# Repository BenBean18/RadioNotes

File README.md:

# KQ4TVW's radio notes
This is an attempt to put much of the random radio knowledge I'm trying to collect in one place for future reference. Radio is really hard and there are so many different things to understand and keep track of, so I thought I'd create a journal thing. Not sure where this is going to go, but I'll probably update this README when I find out :)

## Topics
- [Signal processing](dsp/)
- [Antenna design](antenna/)
- [Amplifier design](amplifier/)
- [Filter design](filter/)
- [Practical usage/application (tools, resources, etc)](application/)

I'm sure I'll think of more things to add, this is a WIP.

## Useful general resources
- https://pysdr.org/index.html
- https://www.electronics-notes.com/articles/radio/rf-mixer/fet-rf-mixer.php
- https://hackaday.com/2020/07/17/modern-radio-receiver-architecture-from-regenerative-to-direct-conversion/
- https://people.physics.anu.edu.au/~dxt103/160m/class_E_amplifier_design.pdf SATURATION VOLTAGE IS ZERO FOR A FET 

## [Journal](journal/)

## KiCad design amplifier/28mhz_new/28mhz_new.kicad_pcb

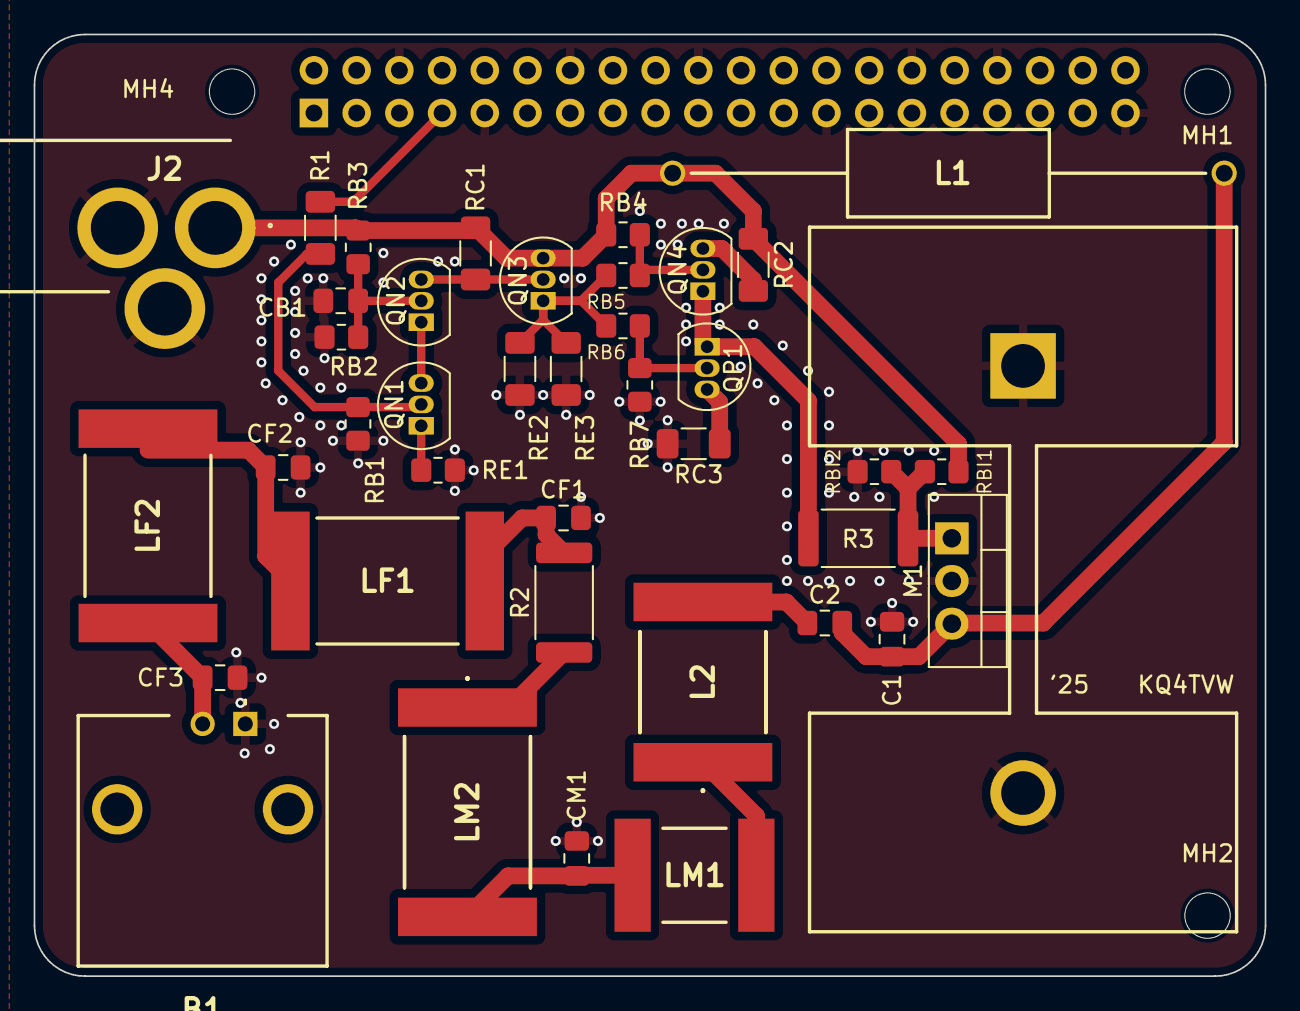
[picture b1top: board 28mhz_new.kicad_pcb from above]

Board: 2 copper layers, 73.2 x 56.0 mm, 44 parts (1 on the bottom side), 25 nets.

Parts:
B1: CONBNC002
C1: 220p; C_0805_2012Metric_Pad1.18x1.45mm_HandSolder
C2: 110p; C_0805_2012Metric_Pad1.18x1.45mm_HandSolder
CB1: 0.022µ; C_0805_2012Metric_Pad1.18x1.45mm_HandSolder
CF1, CF3: 120p; C_0805_2012Metric_Pad1.18x1.45mm_HandSolder
CF2: 220p; C_0805_2012Metric_Pad1.18x1.45mm_HandSolder
CM1: 220p; C_0805_2012Metric_Pad1.18x1.45mm_HandSolder
H1: 647-25ABPE; 64725ABPE
J1: GPIO; PinSocket_2x20_P2.54mm_Vertical
J2: 694106301002; 694106301002_1
L1: 10µ; INDAD3280W80L1200D520
L2: 330n; 2929SQ331GEC
LF1, LF2: 390n; 2929SQ391GEC
LM1: 180n; 2222SQ181JEC
LM2: 430n; 2929SQ431GEC
M1: RD16HHF1; TO-220-3_Vertical
MH1, MH2, MH4: MountingHole_2.7mm_M2.5
QN1, QN2, QN3, QN4: 2N3904; TO-92L_Inline
QP1: 2N3906; TO-92L_Inline
R1: 330; R_1206_3216Metric_Pad1.30x1.75mm_HandSolder
R2, R3: 0; R_2512_6332Metric
RB1: 1k; R_0805_2012Metric_Pad1.20x1.40mm_HandSolder
RB2: 3.3k; R_0805_2012Metric_Pad1.20x1.40mm_HandSolder
RB3: 10k; R_0805_2012Metric_Pad1.20x1.40mm_HandSolder
RB4, RB7: 4.7k; R_0805_2012Metric_Pad1.20x1.40mm_HandSolder
RB5, RB6: 100; R_0805_2012Metric_Pad1.20x1.40mm_HandSolder
RBI1, RBI2: R_0805_2012Metric_Pad1.20x1.40mm_HandSolder
RC1: 330; R_1206_3216Metric_Pad1.30x1.75mm_HandSolder
RC2, RC3: 50; R_1206_3216Metric_Pad1.30x1.75mm_HandSolder
RE1: 33; R_0805_2012Metric_Pad1.20x1.40mm_HandSolder
RE2, RE3: 330; R_1206_3216Metric_Pad1.30x1.75mm_HandSolder

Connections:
0: B1.1, C1.2, CB1.2, CF1.2, CF2.2, CF3.2, CM1.2, H1.1, H1.2, J1.6, J1.9, J1.14, J1.20, J1.25, J1.30, J1.34, J1.39, J2.2 (GND_1), J2.3 (GND_2), M1.2 (S), RB1.2, RB2.2, RB7.2, RBI2.2, RC3.2, RE1.2, RE2.2, RE3.2
+3V3: J1.1, J1.17
+5V: J1.2, J1.4
/GPIO4/GPCLK0: J1.7, R1.2
/RF_OUT: B1.2, CF3.1, LF2.1
/VCC: J2.1 (POWER), L1.1, QN3.3 (C), RB3.1, RB4.1, RBI1.2, RC1.1, RC2.1
unnamed: C2.1, L2.2
unnamed: CF1.1, LF1.2, R2.2
unnamed: CF2.1, LF1.1, LF2.2
unnamed: CM1.1, LM1.1, LM2.2
unnamed: L2.1, LM1.2
unnamed: LM2.1, R2.1
unnamed: C1.1, C2.2, L1.2, M1.3 (D)
unnamed: M1.1 (G), R3.2, RBI1.1, RBI2.1
unnamed: QN1.2 (B), R1.1, RB1.1
unnamed: QN1.3 (C), QN2.1 (E)
unnamed: QN1.1 (E), RE1.1
unnamed: CB1.1, QN2.2 (B), RB2.1, RB3.2
unnamed: QN2.3 (C), QN3.2 (B), RC1.2
unnamed: QN3.1 (E), RB5.2, RB6.1, RE2.1, RE3.1
unnamed: QN4.2 (B), RB4.2, RB5.1
unnamed: QN4.3 (C), RC2.2
unnamed: QN4.1 (E), QP1.1 (E), R3.1
unnamed: QP1.2 (B), RB6.2, RB7.1
unnamed: QP1.3 (C), RC3.1

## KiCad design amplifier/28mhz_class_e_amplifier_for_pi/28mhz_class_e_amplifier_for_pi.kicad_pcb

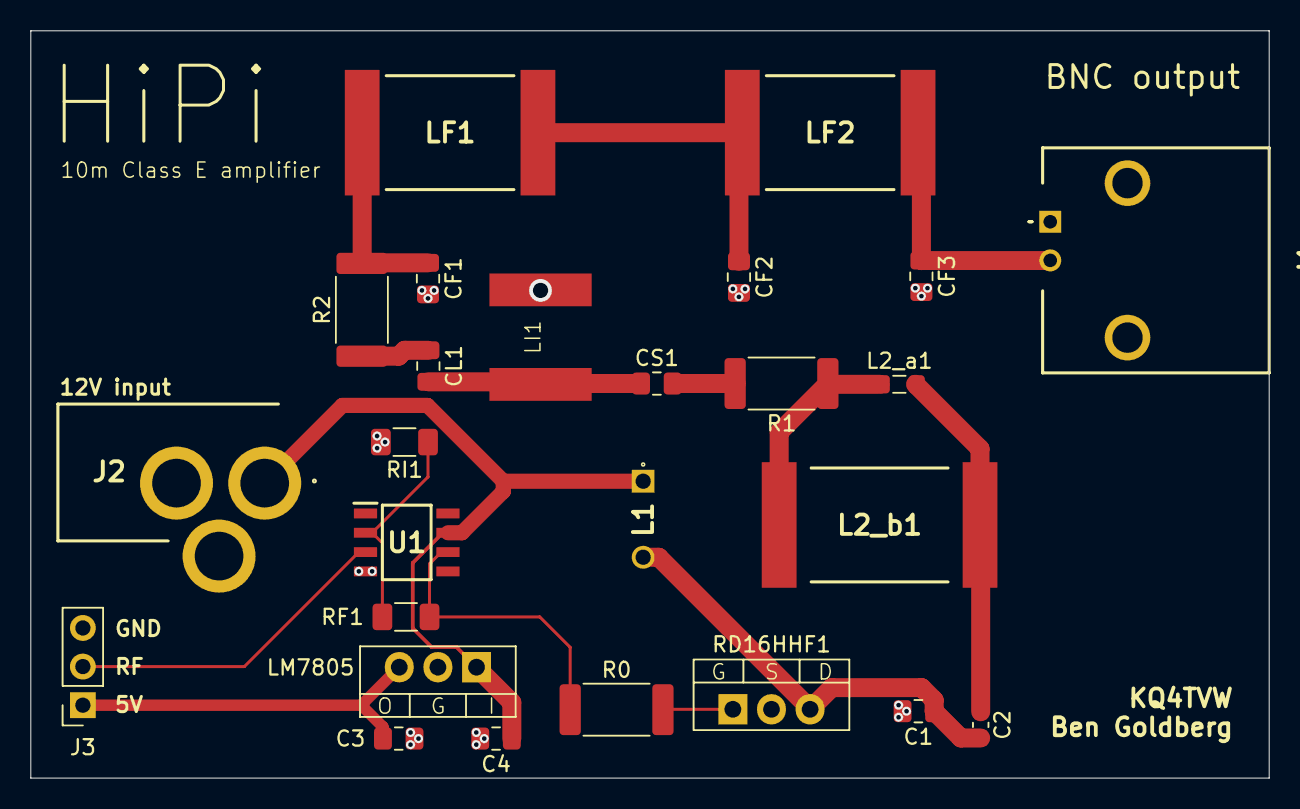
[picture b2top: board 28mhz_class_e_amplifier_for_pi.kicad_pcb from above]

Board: 2 copper layers, 81.5 x 49.2 mm, 26 parts (0 on the bottom side), 16 nets.

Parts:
C1: 10p; C_0805_2012Metric_Pad1.18x1.45mm_HandSolder
C2: 100pF; C_0603_1608Metric_Pad1.08x0.95mm_HandSolder
C3: 0.1u; C_0805_2012Metric_Pad1.18x1.45mm_HandSolder
C4: 0.33u; C_0805_2012Metric_Pad1.18x1.45mm_HandSolder
CF1, CF3: 120p; C_0805_2012Metric_Pad1.18x1.45mm_HandSolder
CF2: 220p; C_0805_2012Metric_Pad1.18x1.45mm_HandSolder
CL1: 110p; C_0805_2012Metric_Pad1.18x1.45mm_HandSolder
CS1: 200p; C_0805_2012Metric_Pad1.18x1.45mm_HandSolder
J1: Conn_Coaxial_Small; CONBNC002
J2: 694106301002; 694106301002_1
J3: Conn_01x03_Socket; PinSocket_1x03_P2.54mm_Vertical
L1: 10µH; B82144B__6.5D_
L2_a1: 1.5µ; L_0805_2012Metric_Pad1.05x1.20mm_HandSolder
L2_b1: 500n; 2929SQ501GEC
LF1, LF2: 390n; 2929SQ391GEC
LI1: 130n; 130nH_WLQC2222H0GR13LB
LM7805: LM7805_TO220; TO-220-3_Vertical
R0, R1, R2: 0; R_2512_6332Metric_Pad1.40x3.35mm_HandSolder
RD16HHF1: RD16HHF1; TO-220-3_Vertical
RF1: 3.3k; R_1206_3216Metric_Pad1.30x1.75mm_HandSolder
RI1: 1k; R_1206_3216Metric_Pad1.30x1.75mm_HandSolder
U1: LT1818; SOIC127P599X175-8N

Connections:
0: C1.2, C3.2, C4.2, CF1.2, CF2.2, CF3.2, J1.1 (In), J2.2 (GND_1), J2.3 (GND_2), J3.3, LI1.2, LM7805.2 (GND), RD16HHF1.1 (D), RI1.2, U1.4 (VCC)
unnamed: C2.1, L2_a1.2, L2_b1.2
unnamed: CF1.1, LF1.2, R2.2
unnamed: CF2.1, LF1.1, LF2.2
unnamed: CL1.1, R2.1
unnamed: CL1.2, CS1.1, LI1.1
unnamed: CS1.2, R1.2
unnamed: CF3.1, J1.2 (Ext), LF2.1
unnamed: C4.1, J2.1 (POWER), L1.1, LM7805.1 (VI), U1.7
unnamed: C3.1, J3.1, LM7805.3 (VO)
unnamed: J3.2, U1.3 (OUT)
unnamed: L2_a1.1, L2_b1.1, R1.1
unnamed: C1.1, C2.2, L1.2, RD16HHF1.3 (S)
unnamed: R0.2, RD16HHF1.2 (G)
unnamed: RF1.2, RI1.1, U1.2 (IN-)
unnamed: R0.1, RF1.1, U1.6

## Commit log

2024-11-12 Initial commit (sampling & start of journal)
2024-11-12 fix paths
2024-11-12 Write a bit about modulation
2024-11-13 Add new ISS observations
2024-11-14 Update journal
2024-11-15 womp womp
2024-11-16 today's escapades
    should probably use LFS for videos but whatever
2024-11-17 I WANT TO DO DXING THIS IS SO COOL
    ISS? 254 miles?
    nah I'd rather receive signals from 6502 miles away in Cabinda, Angola and 2910 miles away (Sao Miguel Island, Azores Islands) on 14.074 MHz using the Watts drainpipe as an antenna
    I want to get my General license now
    I should probably build a transmitter for Tech bands first though :)
2024-11-18 holy ft8
    (Angola, Russia, Brazil, Italy)
2024-11-18 WE DID IT!!!!!
    Received all 12 images
    + FT8 messages from Angola, the Azores Islands, Russia, Italy, the Dominican Republic, the UN, Canada, and a bunch of states
2024-11-19 amplifiers are hard
    and I should really do this more often (making time to deeply research and take detailed notes), it's so helpful for learning but i don't often make time to do it
    cool to learn how stuff works
2024-11-19 backup
2024-11-19 better opti
2024-11-19 stuffs
2024-11-19 i try
2024-11-19 current notes
2024-11-20 10 meter Class A!
2024-11-20 Class E at 3v3
2024-11-20 IT WORKY WITH REAL COMPONENTS
2024-11-20 Impedance matching and LPF
2024-11-20 in progress
2024-11-20 progress
2024-11-20 Begin PCB design
2024-11-20 Switch to 50 ohm impedance
2024-11-21 current progress
    footprints defined for everything except antenna and battery connectors
2024-11-21 ALL FOOTPRINTS ASSIGNED WE ARE COOKING
    still need voltage regulator for Pi, it's ok :D
2024-11-21 Everything except routing done
2024-11-21 almost done, probably
    check pinouts, op amp might be peculiar
2024-11-22 more design
2024-11-22 fix transistor pinout, probably sleep soon
    this is hard and i don't want to frick up since shipping is really expensive
    TODO check preamp, then check over entire circuit, then order PCBs (JLCPCB), components (Mouser), power hardware (Amazon?), BNC cable (Amazon?), antenna, soldering iron (Pinecil?), uhhhhh why is gett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
2024-11-22 fancy text(TM)
2024-11-23 ready for ordering!
    just fixed BNC polarity and untented vias
2024-11-24 think more maybe
2024-11-25 midnight listening
2024-11-26 latest shenanigans
    being able to use normal sampling and the LNA for HF is so helpful!!
2024-11-28 pondering
2025-07-19 backup?
2025-07-23 plane
2025-07-23 More thinking and fix a dumb
2025-07-24 More biasing things, 5W amp now maybe? 2N3904 rise itme of 35ns likely too slow though:
2025-07-24 back2
2025-07-24 maybe works?
2025-07-24 backup i'm tired
2025-07-25 draft3 looks maybe promising
2025-07-25 this actually looks good somehow.
2025-07-25 Make beta not insane so that we don't exceed gain-bandwidth product
2025-07-25 This looks good
2025-07-25 Add choke
2025-07-25 Reminder about resistor power ratings
2025-07-25 notes
2025-07-26 more thinking idk but this looks good
2025-07-26 try things
2025-07-26 seems good?
2025-07-26 165 ohms is better
2025-07-26 Realized that biasing RD16HHF1 at ~5.3V means that it's always on when no AC current.
    So, added another transistor to switch on or off the 12V side of that
    biasing resistor so that we can power on the amplifier w/out a signal
    without it burning up.
    Note: it's another common emitter so active low, make sure to drive it
    high before turning 12V on
2025-07-27 discovered a broken RD16HHF1, probably
2025-07-27 notes of sadness
2025-07-27 more thinking
2025-07-31 /shrug
2025-08-02 scope!
2025-08-03 cascode with trial and error resistor values seems to work in sim?
2025-08-03 i think this might maybe work, using all 3 common types of bjt amplifiers (common emitter feeds into a common base to make a cascode and output of that feeds into common collector as a voltage buffer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
2025-08-03 yeehaw?
2025-08-03 wheeeee learning!
2025-08-03 wheeeee writing!
2025-08-03 goodbye DC bypass caps, now we can turn it off
2025-08-03 -1 RD16HHF1
2025-08-04 wheeeeee
2025-08-04 yipppee!
2025-08-04 wheee
2025-08-05 oscilloscope data!
2025-08-06 Put schematic into KiCAD
2025-08-06 Assigned all footprints
2025-08-06 -1th iteration of pcb design
2025-08-06 This looks nice, but I'm realizing soldering it will be basically impossible
2025-08-07 NO DRC ERRORS
2025-08-07 woohoo now just need power connector
2025-08-07 moved a few things further apart
2025-08-07 SEND IT (in the morning once i have sanity checked)
2025-08-07 Add zero ohm resistors
2025-08-07 Fill some empty space
2025-08-07 sign pcb and write order :)
2025-08-07 Add ground vias
2025-08-07 Fix 3904 and 3906 transistor pinout
2025-08-07 Add mounting holes
2025-08-07 Add places for bias resistors for RD16HHF1
2025-08-07 Generate Gerber and drill files
2025-08-07 Generate Gerber and drill files again
2025-08-07 SEND IT
2025-08-12 ~~failure~~ more learning opportunities await
2025-08-13 zener zener zener zener zeeeeneenenenner
